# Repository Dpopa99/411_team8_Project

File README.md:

* Group Member Names: David Popa | Jade Nguyen | Pushpesh Sharma | Shyamal Singh
* Title: ElectroBoom
* Course: ECE411 Fall 2022
* Date: Oct 13, 2022
* Revision: Version 1.0

# Problem Statement and Concept of Operations
Self defense is a necessity in our everyday lives. Whether you go on late night walks in downtown or spend your time in the rural side of town, you have to be prepared to defend yourself in a attack on your person. The stun gun in its mounted state creates a non-lethal electric shock used to stop an intruder from trespassing in an unauthorized area. The device is connected to an entrance door and upon activation of the device, any unauthorized operation of the door will send an electric shock from the device to the door thus immobilizing the assailant. Although they lack some advantages, such as the capacity to render an adversary helpless or a larger range, they are highly regarded for their ease of use and accessibility. The device is mounted, its size and weight make it portable and versatile. The overall product offers a sense of security and vigilance and should be marketed as such. The final marketing team should strongly consider any number of regulations as well as the variance in stand your ground laws within the U.S and internationally. 

# Market Analysis 
As a mounted device, it can be used by a vast number of customers such as small businesses owners, street food vendors, landlords, storage units owners, RV/Van campers, etc. to protect their belongings and themselves.
Over the development of the product, it can be marketed to bigger businesses, corporate offices, banks, armored vehicles, private security firms, as well as in home security companies. 

The competition can be felt through any of the manufacturers selling pre-installed security devices as well as products that offer multipurpose use such as the Ring Doorbell etc. Our product is in a completely different region as it targets a specific audience: the self-made individuals who are vigilant and don't hesitate to do what's necessary to protect what's theirs. 
	
In comparison to other security devices and their features, our device can be priced within the $40-$50 range. There are several key factors that affect this price and as our design and overall ideas develop, the price may be adjusted accordingly. Factors like the mounting apparatus, 3D printed casing, any user interfaces used, and the cost of internal parts such as the transformer, connectors, and the PCB will eventually determine the final price for our product. 

# Product Requirements
* Must be a rugged design for versatile use and placement.
* Must send a non-lethal electric shock.
* Must be marketed as a plug in device. 
* Must not overheat. (Check transformer behavior in various situations)
* Must be operated via a Door actuated sensor. 
* Should have the ability to be deactivated via remote or physical switch. 
* Should have LED indicators to dictate state of device (Armed or Disarmed)
* May have 3D printed enclosure for all components
* May have Display to show state of device (Active, Triggered, Inactive)

# System Architecture (Currently in Design)

# Design Specification
* Sensor: Door knob movement actuating motion sensor, metal contact to send electric shock
* Processor: ATMega328P microcontroller with Arduino IDE for processing motion sensor activity to send electric shock via transformer. Firmware used will be the Bootloader.  
* Actuator: High voltage transformer taking input voltage and sending converted voltage at variable frequency chosen shock apparatus. 
* Power: 9V wall adapter feeding a high voltage transformer 

# Breadboard Prototype

 As seen from pictures above, the prototype is about finished and all that is needed to have a fully working prototype is the transformer (parts on their way). Image 1 shows the green LED on while the two door sensors are attached, this indicates that the system is armed and ready to go. In the second image, a red LED is shown, meaning that the door has been triggered and the voltage would be discharged out of the two open prongs that would be if the transformer parts were obtained. The video below shows the working prototype.
 
 Current status 11/02/2022: We are awaiting the arrival of our 3.3V to 2000V transformer, upon arrival, we will assemble, test, and commit this transformer to our circuit. Along with this transformer, we will run tests to ensure that the voltage and current combinations will be safe for human contact, however, it is still reccomended that all testing be done by non-human contact, for the safety of our staff, faculty, and students. 

https://user-images.githubusercontent.com/115689153/199646965-d1418cc2-3406-4b21-8939-66e534c145ff.mov

# License
GNU General Public License v2.0
The GNU GPL is the most widely used free software license and has a strong copyleft requirement. When distributing derived works, the source code of the work must be made available under the same license. There are multiple variants of the GNU GPL, each with different requirements.

See Documentation file in this repository for all sources used for this project

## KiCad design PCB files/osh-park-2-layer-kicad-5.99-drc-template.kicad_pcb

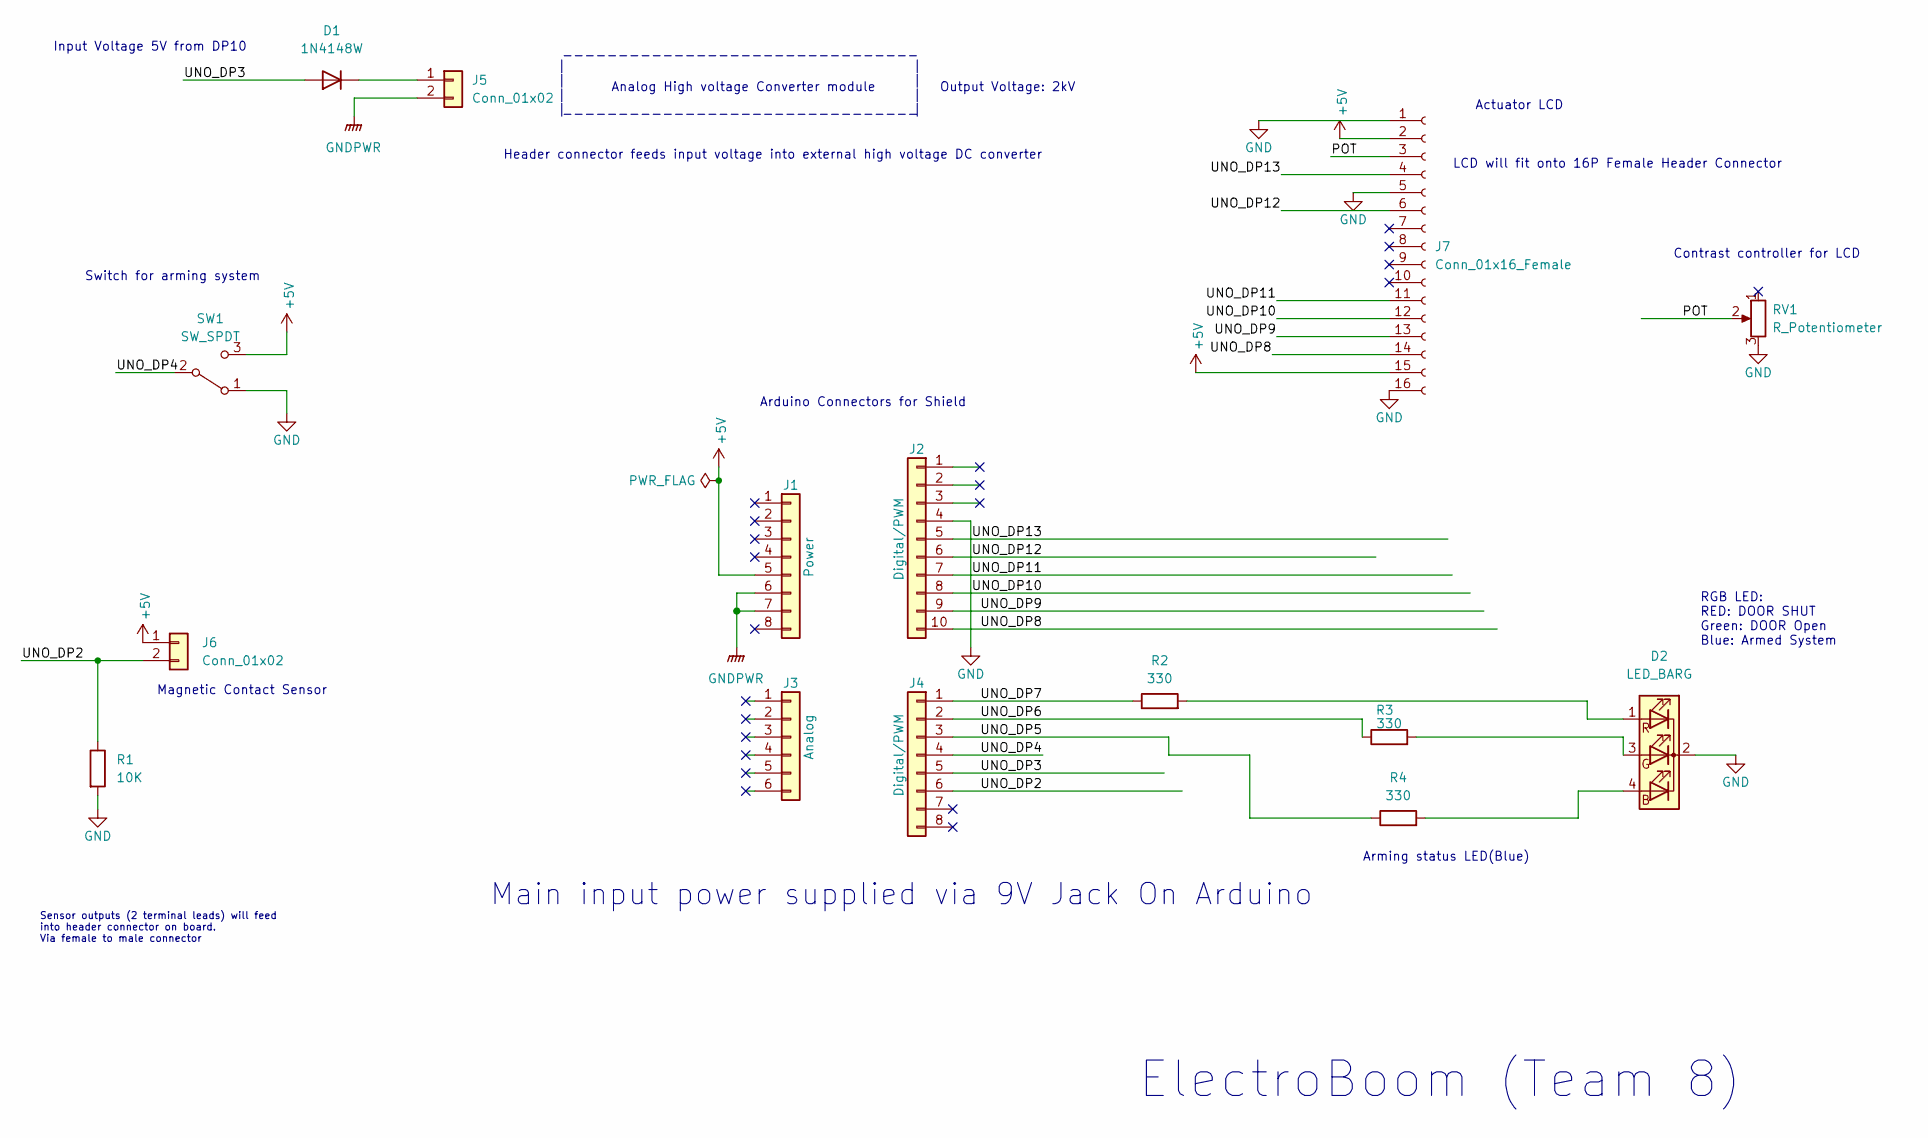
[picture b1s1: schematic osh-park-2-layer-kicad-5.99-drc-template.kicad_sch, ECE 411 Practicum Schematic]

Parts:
D1: 1N4148W; D_SOD-123
D2: LED_BARG; LED_D5.0mm-4_RGB_Wide_Pins
J1: Power; PinSocket_1x08_P2.54mm_Vertical
J2: Digital/PWM; PinSocket_1x10_P2.54mm_Vertical
J3: Analog; PinSocket_1x06_P2.54mm_Vertical
J4: Digital/PWM; PinSocket_1x08_P2.54mm_Vertical
J5, J6: Conn_01x02; PinHeader_1x02_P2.54mm_Vertical
J7: Conn_01x16_Female; PinHeader_1x16_P2.54mm_Vertical
R1: 10K; R_0805_2012Metric
R2, R3, R4: 330; R_0805_2012Metric
RV1: R_Potentiometer; TRIM_3362P-1-505LF
SW1: SW_SPDT; EG1218

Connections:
+5V: J1.5, J6.1, J7.2, J7.15, SW1.3 (C)
/POT: J7.3, RV1.2
/UNO_DP2: J4.6, J6.2, R1.1
/UNO_DP3: D1.2 (A), J4.5
/UNO_DP4: J4.4, SW1.2 (B)
/UNO_DP5: J4.3, R4.1
/UNO_DP6: J4.2, R3.1
/UNO_DP7: J4.1, R2.1
/UNO_DP8: J2.10, J7.14
/UNO_DP9: J2.9, J7.13
/UNO_DP10: J2.8, J7.12
/UNO_DP11: J2.7, J7.11
/UNO_DP12: J2.6, J7.6
/UNO_DP13: J2.5, J7.4
GND: D2.2 (A), J2.4, J7.1, J7.5, J7.16, R1.2, RV1.3, SW1.1 (A)
GNDPWR: J1.6, J1.7, J5.2
unnamed: D1.1 (K), J5.1
unnamed: D2.1 (BK), R2.2
unnamed: D2.3 (RK), R3.2
unnamed: D2.4 (GK), R4.2

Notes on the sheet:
Main input power supplied via 9V Jack On Arduino
RGB LED: RED: DOOR SHUT Green: DOOR Open Blue: Armed System
Input Voltage 5V from DP10
Arduino Connectors for Shield
LCD will fit onto 16P Female Header Connector
| | | |
Arming status LED(Blue)
Output Voltage: 2kV
Header connector feeds input voltage into external high voltage DC converter
Actuator LCD
Analog High voltage Converter module
Switch for arming system
--------------------------------
Contrast controller for LCD
Sensor outputs (2 terminal leads) will feed into header connector on board. Via female to male connector
Magnetic Contact Sensor
ElectroBoom (Team 8)

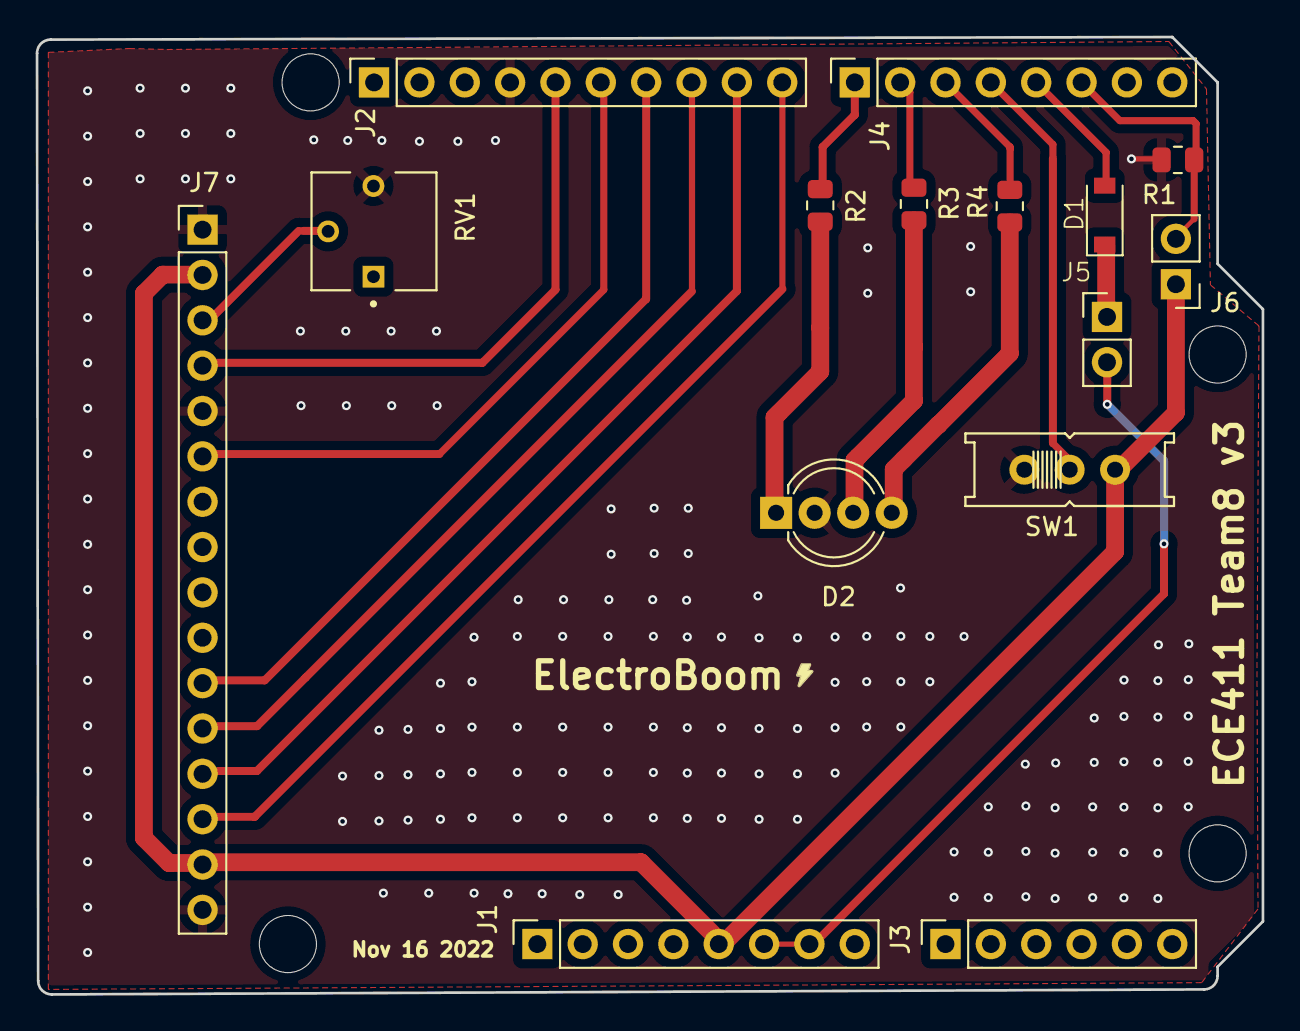
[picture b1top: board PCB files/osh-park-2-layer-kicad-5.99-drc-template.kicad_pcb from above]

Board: 2 copper layers, 68.7 x 53.6 mm, 19 parts (0 on the bottom side), 20 nets.

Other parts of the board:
MH1, MH2, MH3, MH4: MountingHole_3.2mm

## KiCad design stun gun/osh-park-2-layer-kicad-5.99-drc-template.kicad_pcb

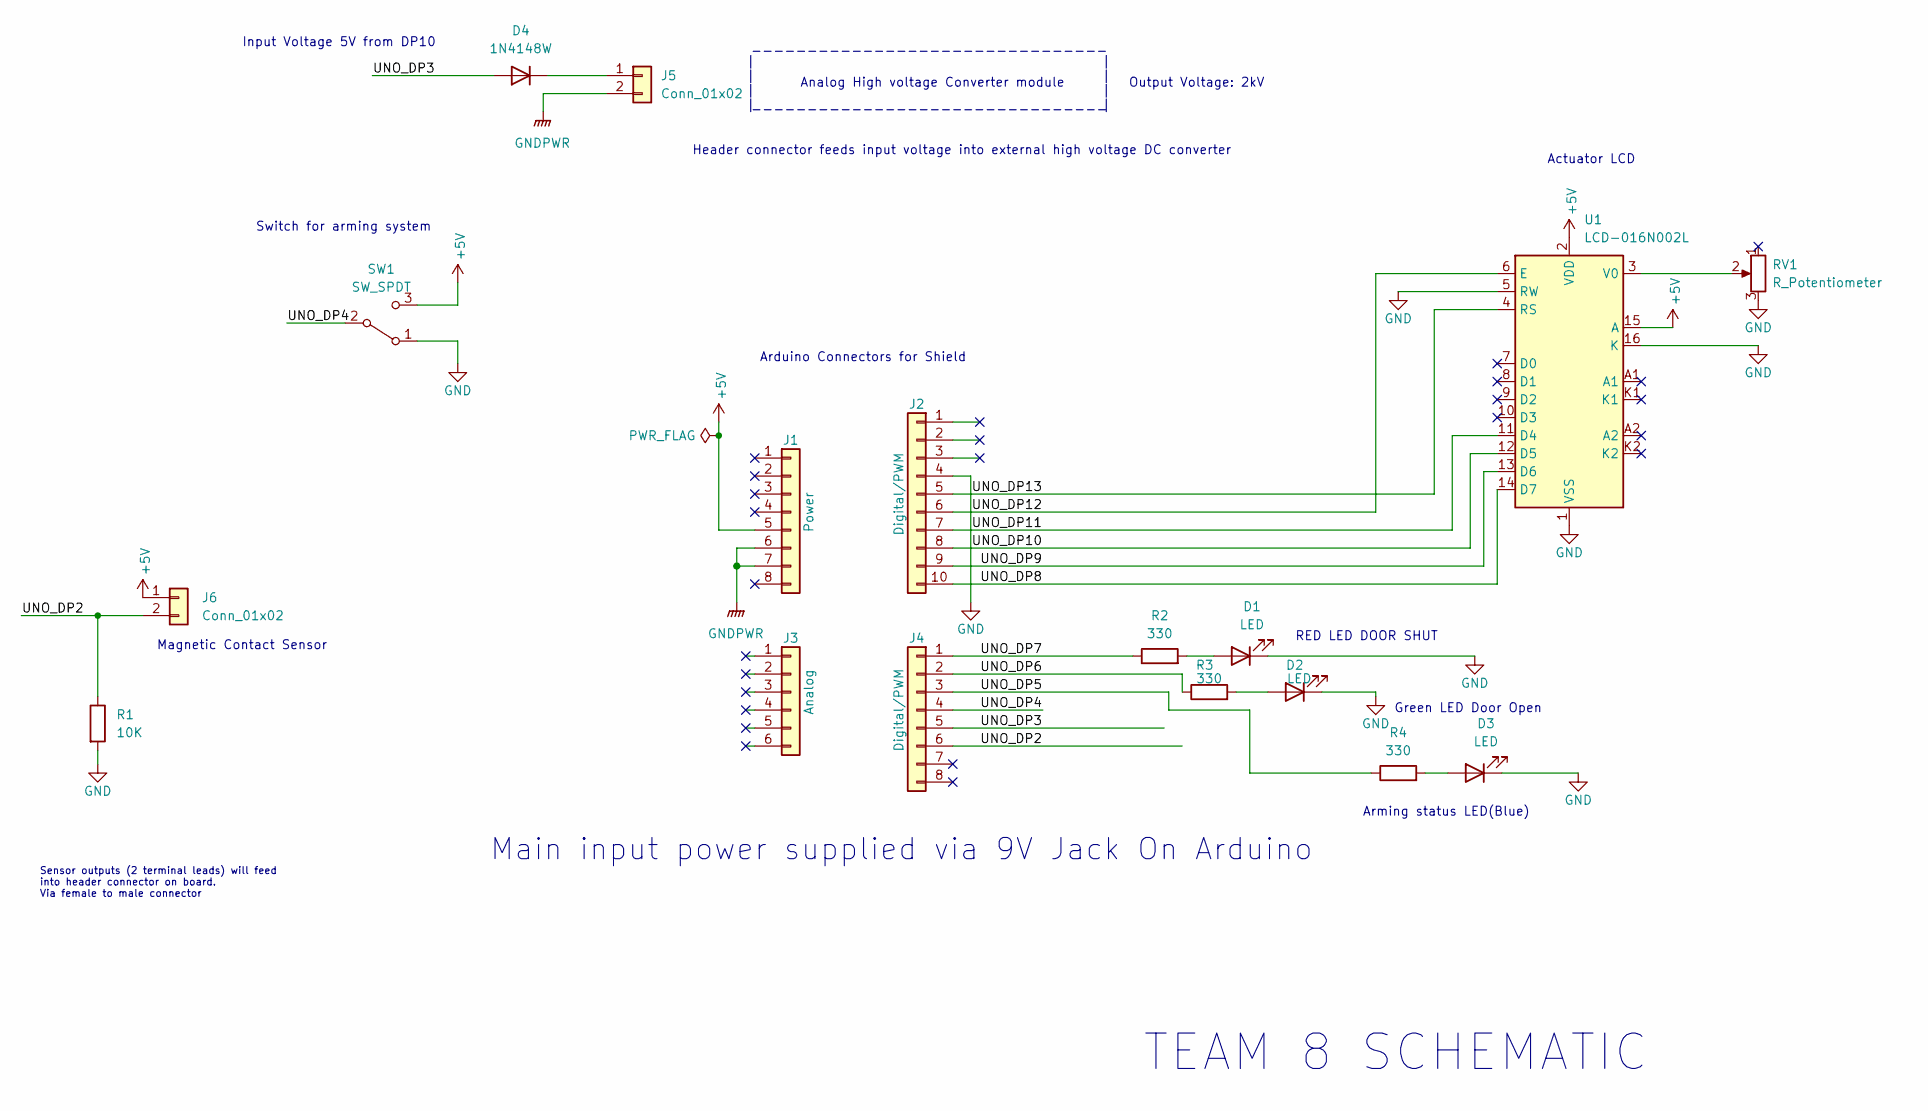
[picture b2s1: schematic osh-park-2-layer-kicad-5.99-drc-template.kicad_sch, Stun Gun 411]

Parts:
D1, D2, D3: LED; LED_D3.0mm
D4: 1N4148W; D_SOD-123
J1: Power; PinSocket_1x08_P2.54mm_Vertical
J2: Digital/PWM; PinSocket_1x10_P2.54mm_Vertical
J3: Analog; PinSocket_1x06_P2.54mm_Vertical
J4: Digital/PWM; PinSocket_1x08_P2.54mm_Vertical
J5, J6: Conn_01x02; PinHeader_1x02_P2.54mm_Vertical
R1: 10K; R_0805_2012Metric
R2, R3, R4: 330; R_0805_2012Metric
RV1: R_Potentiometer; TRIM_3362P-1-505LF
SW1: SW_SPDT; EG1218
U1: LCD-016N002L

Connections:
+5V: J1.5, J6.1, SW1.3 (C), U1.2 (VDD), U1.15 (A)
/UNO_DP2: J4.6, J6.2, R1.1
/UNO_DP3: D4.2 (A), J4.5
/UNO_DP4: J4.4, SW1.2 (B)
/UNO_DP5: J4.3, R4.1
/UNO_DP6: J4.2, R3.1
/UNO_DP7: J4.1, R2.1
/UNO_DP8: J2.10, U1.14 (D7)
/UNO_DP9: J2.9, U1.13 (D6)
/UNO_DP10: J2.8, U1.12 (D5)
/UNO_DP11: J2.7, U1.11 (D4)
/UNO_DP12: J2.6, U1.6 (E)
/UNO_DP13: J2.5, U1.4 (RS)
GND: D1.1 (K), D2.1 (K), D3.1 (K), J2.4, R1.2, RV1.3, SW1.1 (A), U1.1 (VSS), U1.5 (RW), U1.16 (K)
GNDPWR: J1.6, J1.7, J5.2
unnamed: D1.2 (A), R2.2
unnamed: D2.2 (A), R3.2
unnamed: D3.2 (A), R4.2
unnamed: D4.1 (K), J5.1
unnamed: RV1.2, U1.3 (V0)

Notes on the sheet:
Main input power supplied via 9V Jack On Arduino
RED LED DOOR SHUT
Input Voltage 5V from DP10
Green LED Door Open
Arduino Connectors for Shield
| | | |
Arming status LED(Blue)
Output Voltage: 2kV
Header connector feeds input voltage into external high voltage DC converter
Actuator LCD
Analog High voltage Converter module
Switch for arming system
--------------------------------
Sensor outputs (2 terminal leads) will feed into header connector on board. Via female to male connector
Magnetic Contact Sensor
TEAM 8 SCHEMATIC

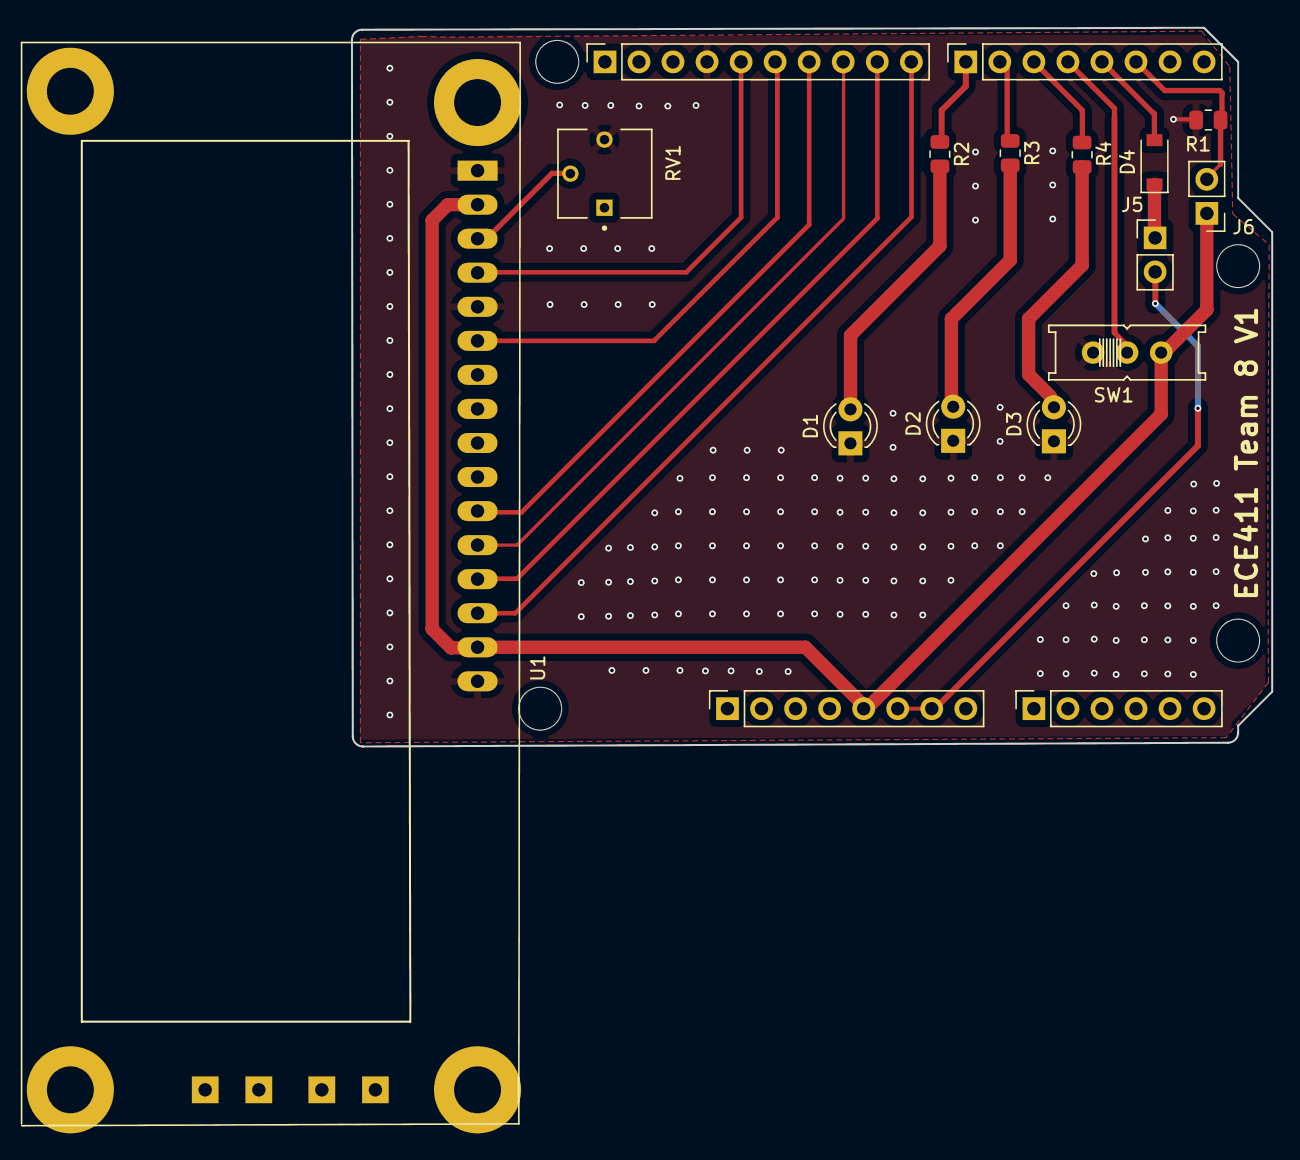
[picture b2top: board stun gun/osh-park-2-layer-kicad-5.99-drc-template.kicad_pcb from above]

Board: 2 copper layers, 68.7 x 53.6 mm, 21 parts (0 on the bottom side), 20 nets.

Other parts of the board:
MH1, MH2, MH3, MH4: MountingHole_3.2mm

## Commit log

2022-10-13 Create Version Control
2022-10-13 Create Issue Tracking
2022-10-13 Create Documentation_and_notes
2022-10-19 Add files via upload
    block diagram version 1
2022-10-27 Add files via upload
    Preliminary Schematic Design
2022-11-03 Create SmartSheet Gantt Chart
2022-11-03 Update and rename SmartSheet Gantt Chart to Project Schedule
2022-11-15 Create BOM
2022-11-17 Add files via upload
    Final version (V3) for layout/schematic
